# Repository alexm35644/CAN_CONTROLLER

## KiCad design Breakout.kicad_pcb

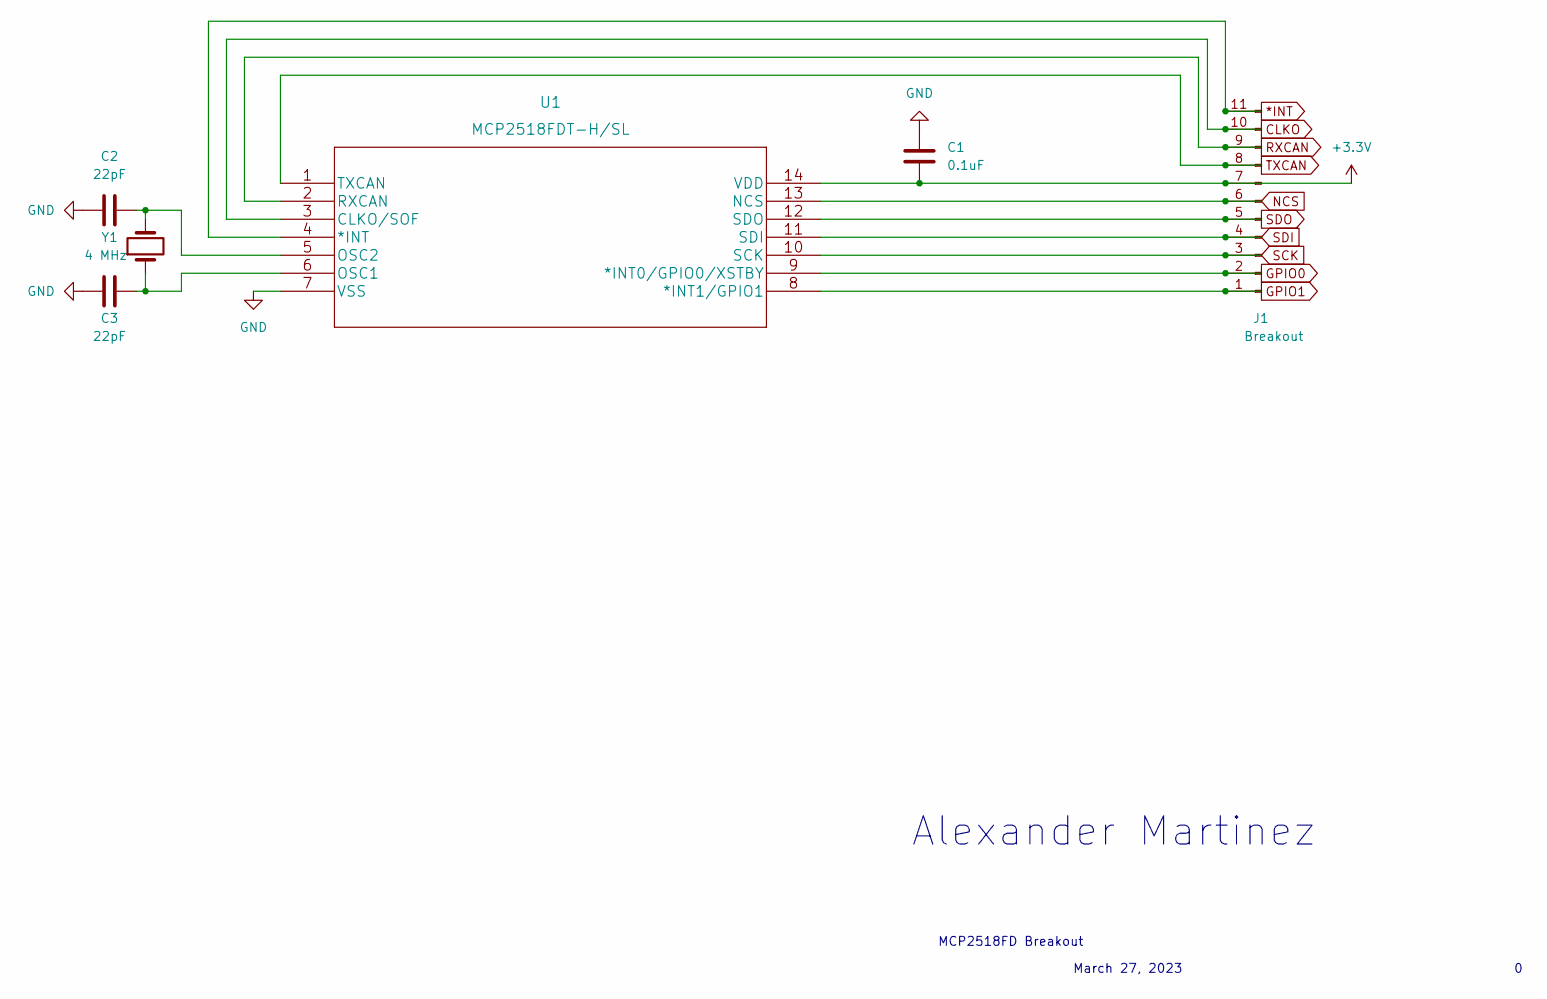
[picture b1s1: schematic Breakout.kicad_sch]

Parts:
C1: 0.1uF; C_0603_1608Metric_Pad1.08x0.95mm_HandSolder
C2, C3: 22pF; C_0603_1608Metric_Pad1.08x0.95mm_HandSolder
J1: Breakout; PinHeader_1x11_P2.54mm_Vertical
U1: MCP2518FDT-H/SL; 14-SOIC
Y1: 4 MHz; HC-49US

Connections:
+3.3V: C1.2, J1.7, U1.14 (VDD)
GND: C1.1, C2.1, C3.1, U1.7 (VSS)
unnamed: C2.2, U1.5 (OSC2), Y1.2
unnamed: C3.2, U1.6 (OSC1), Y1.1
unnamed: J1.1, U1.8 (*INT1/GPIO1)
unnamed: J1.2, U1.9 (*INT0/GPIO0/XSTBY)
unnamed: J1.3, U1.10 (SCK)
unnamed: J1.4, U1.11 (SDI)
unnamed: J1.5, U1.12 (SDO)
unnamed: J1.6, U1.13 (NCS)
unnamed: J1.8, U1.1 (TXCAN)
unnamed: J1.9, U1.2 (RXCAN)
unnamed: J1.10, U1.3 (CLKO/SOF)
unnamed: J1.11, U1.4 (*INT)

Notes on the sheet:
March 27, 2023
Alexander Martinez
MCP2518FD Breakout

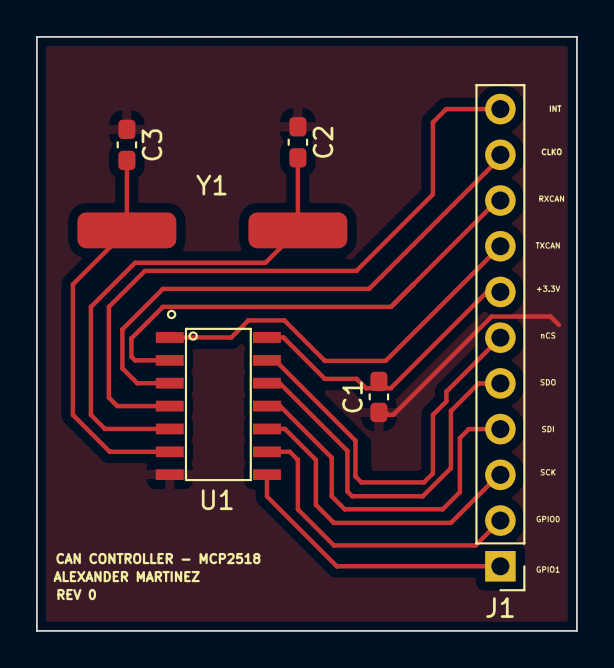
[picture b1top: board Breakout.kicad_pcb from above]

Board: 2 copper layers, 30.0 x 33.0 mm, 6 parts (0 on the bottom side), 14 nets.

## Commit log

2023-03-29 cleaned up
2023-03-29 cleaned ground
